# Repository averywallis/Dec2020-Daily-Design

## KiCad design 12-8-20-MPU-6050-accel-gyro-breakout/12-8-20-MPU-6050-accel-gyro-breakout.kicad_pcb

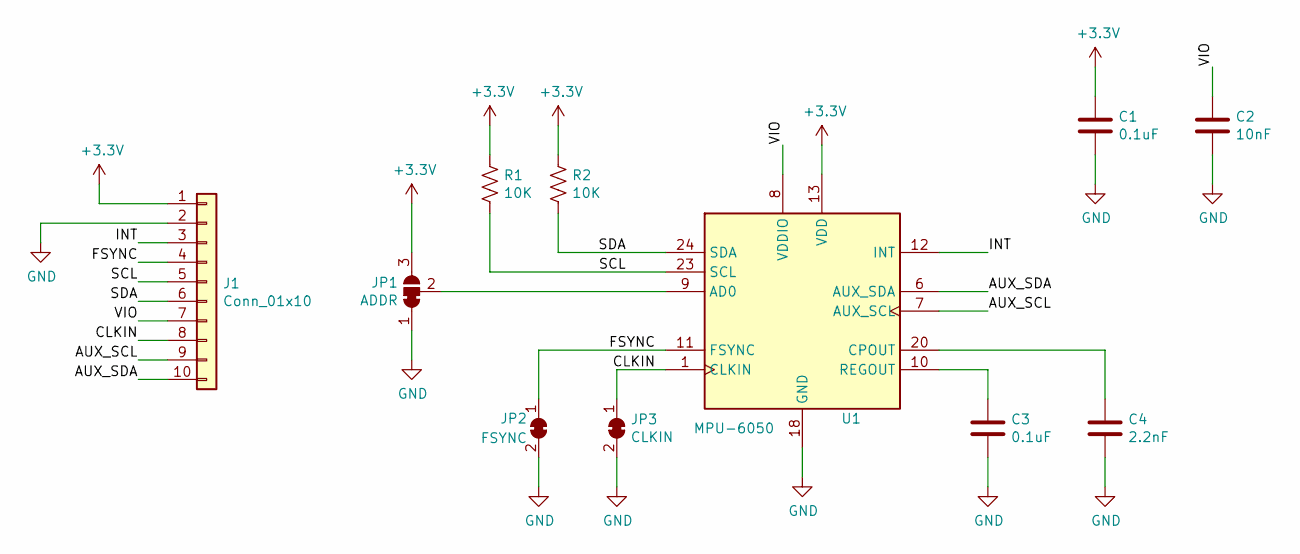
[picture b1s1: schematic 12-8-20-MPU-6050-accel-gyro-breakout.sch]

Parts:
C1, C3: 0.1uF; C_0805_2012Metric
C2: 10nF; C_0805_2012Metric
C4: 2.2nF; C_0805_2012Metric
J1: Conn_01x10; PinHeader_1x10_P2.54mm_Vertical
JP1: ADDR; SolderJumper-3_P1.3mm_Bridged12_RoundedPad1.0x1.5mm
JP2: FSYNC; SolderJumper-2_P1.3mm_Bridged_RoundedPad1.0x1.5mm
JP3: CLKIN; SolderJumper-2_P1.3mm_Bridged_RoundedPad1.0x1.5mm
R1, R2: 10K; R_0805_2012Metric
U1: MPU-6050; InvenSense_QFN-24_4x4mm_P0.5mm

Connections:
+3V3: C1.1, J1.1, JP1.3 (B), R1.1, R2.1, U1.13 (VDD)
/AUX_SCL: J1.9, U1.7 (AUX_SCL)
/AUX_SDA: J1.10, U1.6 (AUX_SDA)
/CLKIN: J1.8, JP3.1 (A), U1.1 (CLKIN)
/FSYNC: J1.4, JP2.1 (A), U1.11 (FSYNC)
/INT: J1.3, U1.12 (INT)
/SCL: J1.5, R1.2, U1.23 (SCL)
/SDA: J1.6, R2.2, U1.24 (SDA)
/VIO: C2.1, J1.7, U1.8 (VDDIO)
GND: C1.2, C2.2, C3.2, C4.2, J1.2, JP1.1 (A), JP2.2 (B), JP3.2 (B), U1.18 (GND)
unnamed: C3.1, U1.10 (REGOUT)
unnamed: C4.1, U1.20 (CPOUT)
unnamed: JP1.2 (C), U1.9 (AD0)

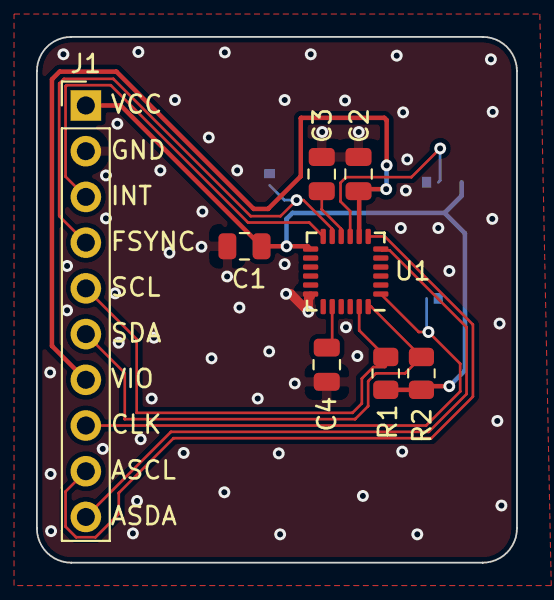
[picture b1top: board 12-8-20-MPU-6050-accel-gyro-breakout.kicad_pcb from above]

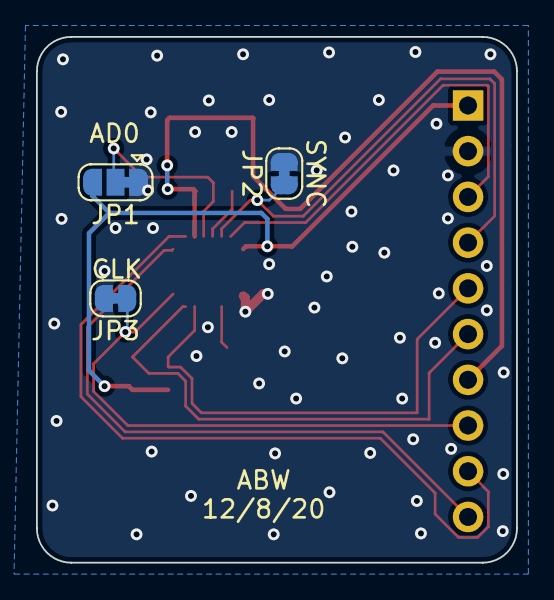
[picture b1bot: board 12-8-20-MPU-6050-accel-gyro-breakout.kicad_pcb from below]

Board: 2 copper layers, 26.7 x 29.2 mm, 11 parts (3 on the bottom side), 13 nets.

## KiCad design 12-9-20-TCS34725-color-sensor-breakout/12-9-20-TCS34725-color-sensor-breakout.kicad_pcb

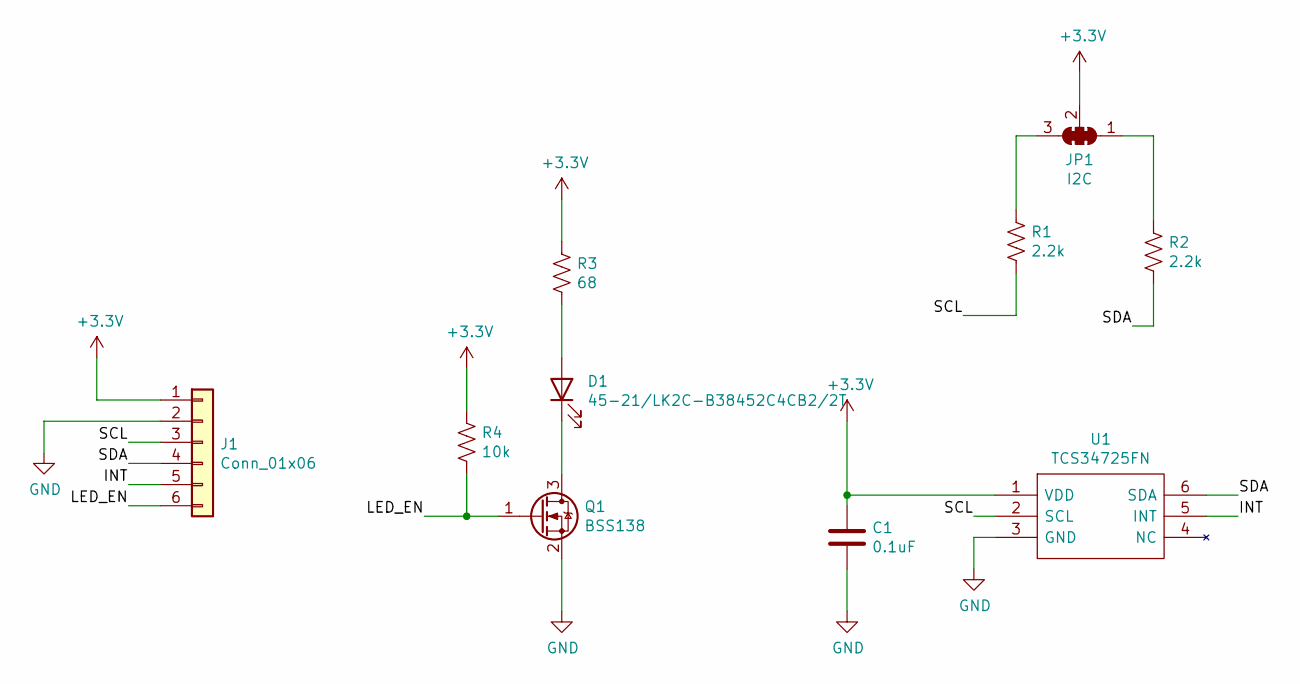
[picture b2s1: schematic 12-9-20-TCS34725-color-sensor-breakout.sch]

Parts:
C1: 0.1uF; C_0805_2012Metric
D1: 45-21/LK2C-B38452C4CB2/2T; LED_0805_2012Metric
J1: Conn_01x06; PinHeader_1x06_P2.54mm_Vertical
JP1: I2C; SMT-JUMPER_3_2-NC_TRACE_SILK
Q1: BSS138; SOT-23
R1, R2: 2.2k; R_0805_2012Metric
R3: 68; R_0805_2012Metric
R4: 10k; R_0805_2012Metric
U1: TCS34725FN; FN_1; Manufacturer_Part_Number TCS34725FN; Mouser Part Number 985-TCS34725FN

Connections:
+3V3: C1.1, J1.1, JP1.2 (C), R3.1, R4.1, U1.1 (VDD)
/INT: J1.5, U1.5 (INT)
/LED_EN: J1.6, Q1.1 (G), R4.2
/SCL: J1.3, R1.2, U1.2 (SCL)
/SDA: J1.4, R2.2, U1.6 (SDA)
GND: C1.2, J1.2, Q1.2 (S), U1.3 (GND)
unnamed: D1.1 (K), Q1.3 (D)
unnamed: D1.2 (A), R3.2
unnamed: JP1.1 (A), R2.1
unnamed: JP1.3 (B), R1.1

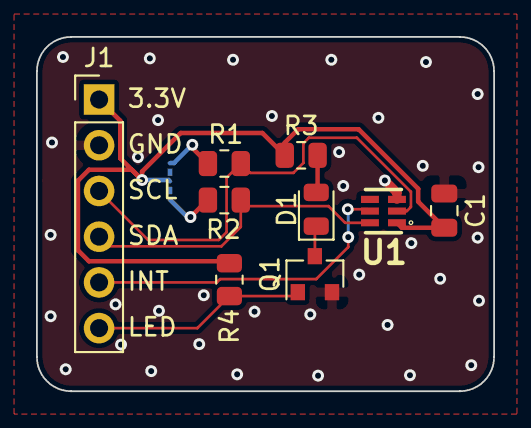
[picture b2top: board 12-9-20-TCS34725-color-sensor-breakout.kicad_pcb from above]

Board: 2 copper layers, 25.4 x 19.7 mm, 10 parts (1 on the bottom side), 10 nets.
